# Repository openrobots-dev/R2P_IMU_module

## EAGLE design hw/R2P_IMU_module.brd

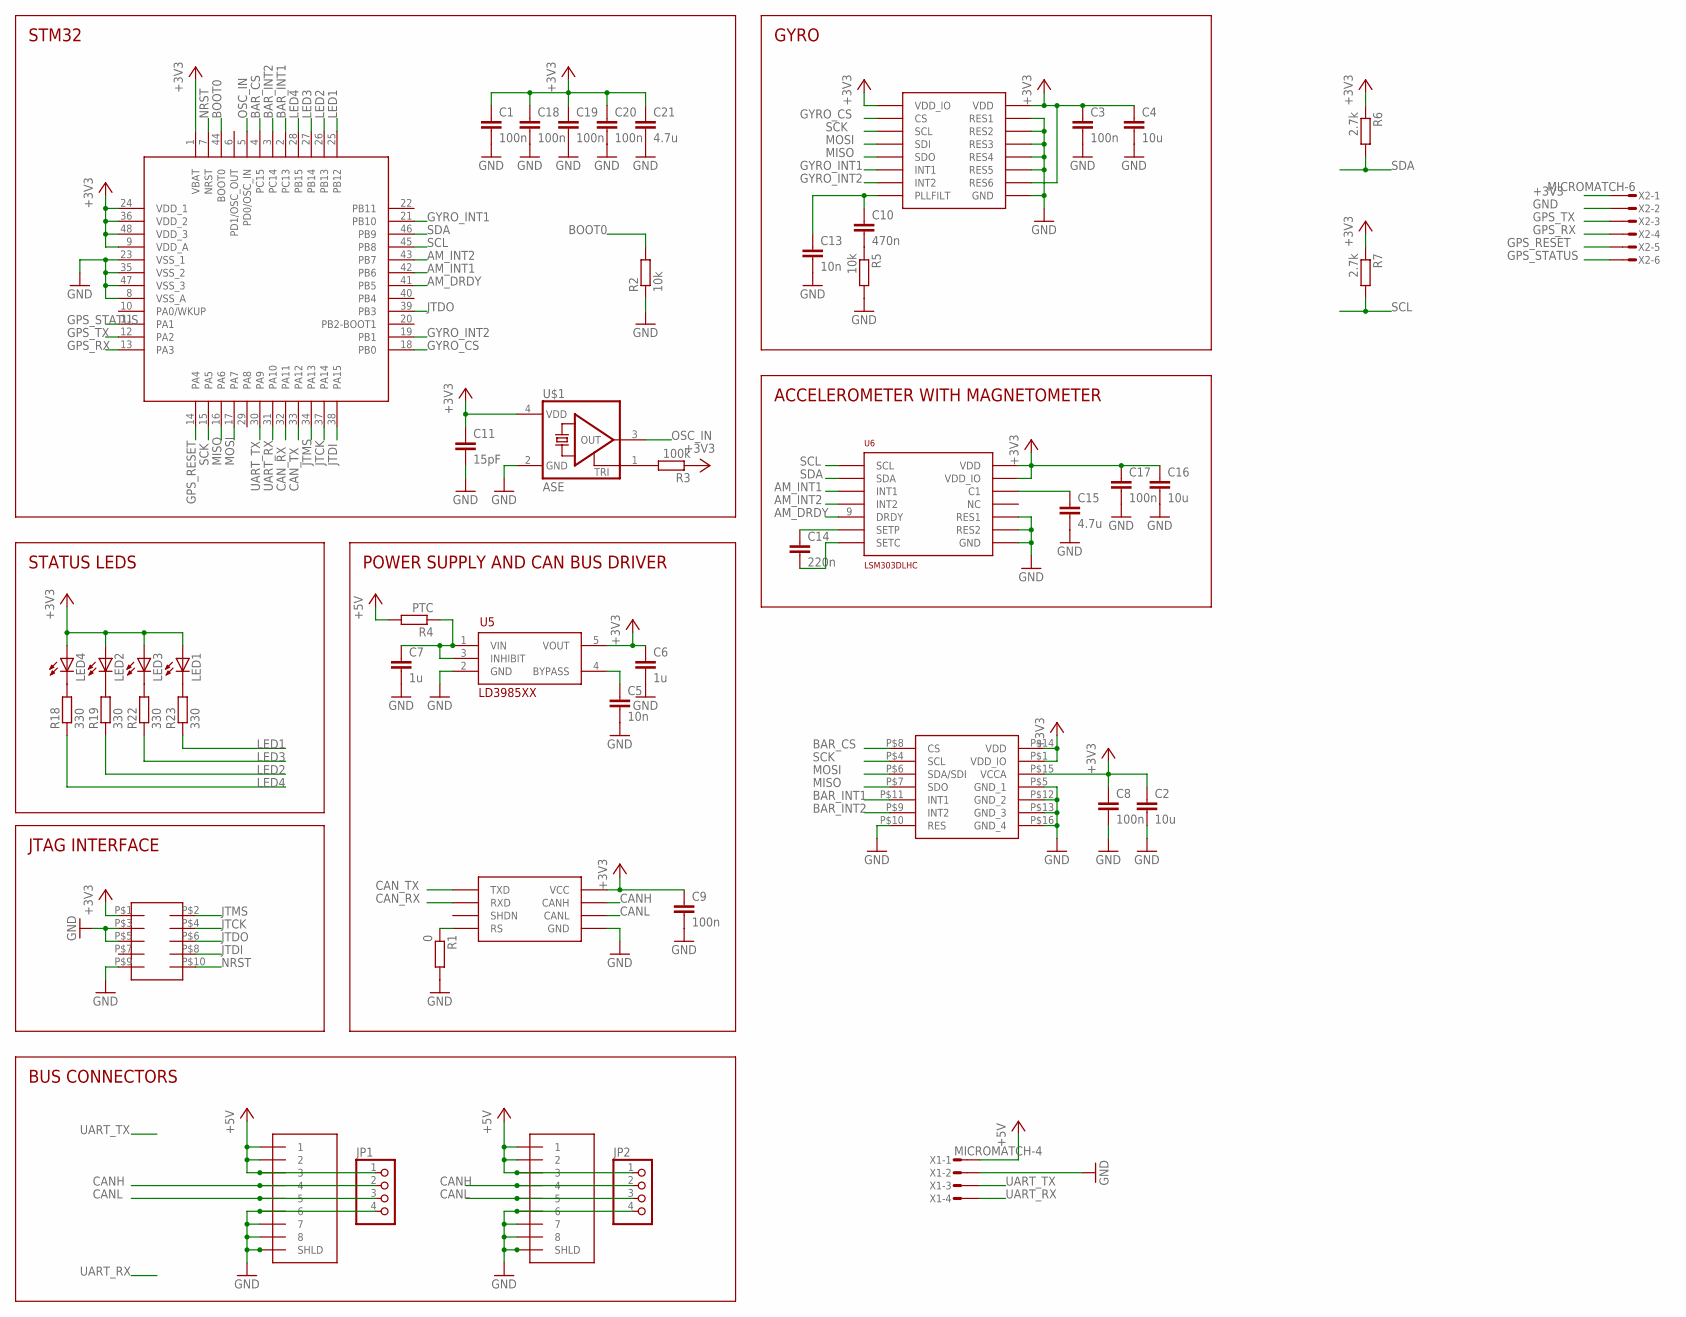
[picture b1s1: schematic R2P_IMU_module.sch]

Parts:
1, 2: RJ45-43860; 0438600010
C1, C3, C8, C9, C17, C18, C19, C20: 100n; C0603
C2, C4, C16: 10u; C0805
C5, C13: 10n; C0603
C6, C7: 1u; C0603
C10: 470n; C0603
C11: 15pF; C0603
C14: 220n; C0603
C15, C21: 4.7u; C0805
JP1, JP2: PINHD-1X4; 1X04
LED1, LED2, LED3, LED4: LEDCHIPLED_0805; CHIPLED_0805
R1: 0; R0603
R2, R5: 10k; R0603
R3: 100k; R0603
R4: PTC; R0603
R6, R7: 2.7k; R0603
R18, R19, R22, R23: 330; R0603
SOT1: MAX3051; SOT23-8L
U1: STM32F103CX; LQFP48
U2: L3G4200D; LGA16
U5: LD3985XX; SOT23-5L
U6: LSM303DLHC; LGA14
U$1: ASE
U$2: LPS331AP; HCLGA16
U$4: FTSH-105
X1: MICROMATCH-4
X2: MICROMATCH-6

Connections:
+3V3: C1.1, C2.1, C3.1, C4.1, C6.1, C8.1, C9.1, C11.1, C16.1, C17.1, C18.1, C19.1, C20.1, C21.1, LED1.A, LED2.A, LED3.A, LED4.A, R3.1, R6.1, R7.1, SOT1.P$3 (VCC), U1.1 (VBAT), U1.9 (VDD_A), U1.24 (VDD_1), U1.36 (VDD_2), U1.48 (VDD_3), U2.P$1 (VDD_IO), U2.P$15 (RES6), U2.P$16 (VDD), U5.5 (VOUT), U6.1 (VDD_IO), U6.14 (VDD), U$1.4 (VDD), U$2.P$1 (VDD_IO), U$2.P$14 (VDD), U$2.P$15 (VCCA), U$4.P$1, X2.1
+5V: 1.P$1 (1), 1.P$2 (2), 1.P$3 (3), 2.P$1 (1), 2.P$2 (2), 2.P$3 (3), JP1.1, JP2.1, R4.2, X1.1
AM_DRDY: U1.41 (PB5), U6.9 (DRDY)
AM_INT1: U1.42 (PB6), U6.5 (INT1)
AM_INT2: U1.43 (PB7), U6.4 (INT2)
BAR_CS: U1.4 (PC15), U$2.P$8 (CS)
BAR_INT1: U1.2 (PC13), U$2.P$11 (INT1)
BAR_INT2: U1.3 (PC14), U$2.P$9 (INT2)
BOOT0: R2.2, U1.44 (BOOT0)
CANH: 1.P$4 (4), 2.P$4 (4), JP1.2, JP2.2, SOT1.P$7 (CANH)
CANL: 1.P$5 (5), 2.P$5 (5), JP1.3, JP2.3, SOT1.P$6 (CANL)
CAN_RX: SOT1.P$4 (RXD), U1.32 (PA11)
CAN_TX: SOT1.P$1 (TXD), U1.33 (PA12)
GND: 1.P$6 (6), 1.P$7 (7), 1.P$8 (8), 1.P$9 (SHLD), 1.P$10, 2.P$6 (6), 2.P$7 (7), 2.P$8 (8), 2.P$9 (SHLD), 2.P$10, C1.2, C2.2, C3.2, C4.2, C5.2, C6.2, C7.2, C8.2, C9.2, C11.2, C13.2, C15.2, C16.2, C17.2, C18.2, C19.2, C20.2, C21.2, JP1.4, JP2.4, R1.2, R2.1, R5.2, SOT1.P$2 (GND), U1.8 (VSS_A), U1.23 (VSS_1), U1.35 (VSS_2), U1.47 (VSS_3), U2.P$8 (RES1), U2.P$9 (RES2), U2.P$10 (RES3), U2.P$11 (RES4), U2.P$12 (RES5), U2.P$13 (GND), U5.2 (GND), U6.7 (GND), U6.10 (RES1), U6.11 (RES2), U$1.2 (GND), U$2.P$5 (GND_1), U$2.P$10 (RES), U$2.P$12 (GND_2), U$2.P$13 (GND_3), U$2.P$16 (GND_4), U$4.P$3, U$4.P$5, U$4.P$9, X1.2, X2.2
GPS_RESET: U1.14 (PA4), X2.5
GPS_RX: U1.13 (PA3), X2.4
GPS_STATUS: U1.11 (PA1), X2.6
GPS_TX: U1.12 (PA2), X2.3
GYRO_CS: U1.18 (PB0), U2.P$5 (CS)
GYRO_INT1: U1.21 (PB10), U2.P$7 (INT1)
GYRO_INT2: U1.19 (PB1), U2.P$6 (INT2)
JTCK: U1.37 (PA14), U$4.P$4
JTDI: U1.38 (PA15), U$4.P$8
JTDO: U1.39 (PB3), U$4.P$6
JTMS: U1.34 (PA13), U$4.P$2
LED1: R23.1, U1.25 (PB12)
LED2: R19.1, U1.26 (PB13)
LED3: R22.1, U1.27 (PB14)
LED4: R18.1, U1.28 (PB15)
MISO: U1.16 (PA6), U2.P$4 (SDO), U$2.P$7 (SDO)
MOSI: U1.17 (PA7), U2.P$3 (SDI), U$2.P$6 (SDA/SDI)
unnamed: R1.1, SOT1.P$8 (RS)
unnamed: R3.2, U$1.1 (TRI)
unnamed: C5.1, U5.4 (BYPASS)
unnamed: C7.1, R4.1, U5.1 (VIN), U5.3 (INHIBIT)
unnamed: C10.2, R5.1
unnamed: C10.1, C13.1, U2.P$14 (PLLFILT)
unnamed: C14.1, U6.12 (SETP)
unnamed: LED4.C, R18.2
unnamed: C14.2, U6.13 (SETC)
unnamed: C15.1, U6.6 (C1)
unnamed: LED2.C, R19.2
unnamed: LED3.C, R22.2
unnamed: LED1.C, R23.2
NRST: U1.7 (NRST), U$4.P$10
OSC_IN: U1.5 (PD0/OSC_IN), U$1.3 (OUT)
SCK: U1.15 (PA5), U2.P$2 (SCL), U$2.P$4 (SCL)
SCL: R7.2, U1.45 (PB8), U6.2 (SCL)
SDA: R6.2, U1.46 (PB9), U6.3 (SDA)
UART_RX: U1.31 (PA10), X1.4
UART_TX: U1.30 (PA9), X1.3

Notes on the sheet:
STM32
POWER SUPPLY AND CAN BUS DRIVER
STATUS LEDS
JTAG INTERFACE
BUS CONNECTORS
ACCELEROMETER WITH MAGNETOMETER
GYRO

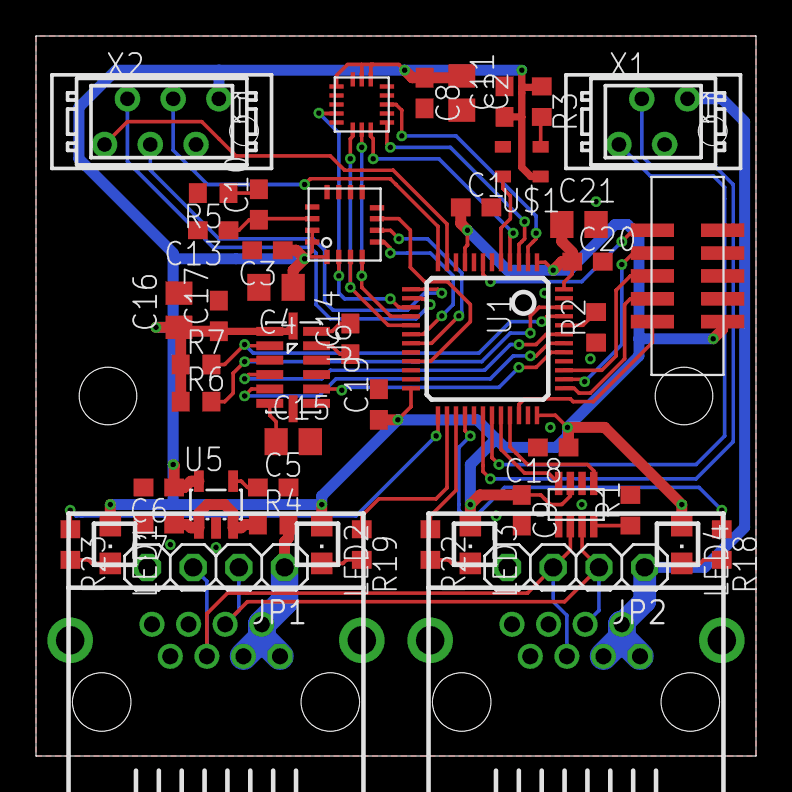
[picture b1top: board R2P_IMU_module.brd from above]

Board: 2 copper layers, 40.0 x 40.0 mm, 49 parts (0 on the bottom side), 51 nets.

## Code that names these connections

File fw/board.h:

/*
 ChibiOS/RT - Copyright (C) 2006,2007,2008,2009,2010,
 2011 Giovanni Di Sirio.

 This file is part of ChibiOS/RT.

 ChibiOS/RT is free software; you can redistribute it and/or modify
 it under the terms of the GNU General Public License as published by
 the Free Software Foundation; either version 3 of the License, or
 (at your option) any later version.

 ChibiOS/RT is distributed in the hope that it will be useful,
 but WITHOUT ANY WARRANTY; without even the implied warranty of
 MERCHANTABILITY or FITNESS FOR A PARTICULAR PURPOSE.  See the
 GNU General Public License for more details.

 You should have received a copy of the GNU General Public License
 along with this program.  If not, see <http://www.gnu.org/licenses/>.
 */

#ifndef _BOARD_H_
#define _BOARD_H_

/*
 * Setup for the R2D IMU module.
 */

/*
 * Board identifier.
 */
#define BOARD_R2P_IMU_MODULE
#define BOARD_NAME              "R2P IMU module"

/*
 * Board frequencies.
 */
#define STM32_LSECLK            32768
#define STM32_HSECLK            8000000

/*
 * MCU type, supported types are defined in ./os/hal/platforms/hal_lld.h.
 */
#define STM32F10X_MD
#define STM32F10X

/*
 * IO pins assignments.
 */
#define LED1_GPIO				GPIOB
#define LED1					12
#define LED2_GPIO				GPIOB
#define LED2					13
#define LED3_GPIO				GPIOB
#define LED3					14
#define LED4_GPIO				GPIOB
#define LED4					15

#define SERIAL_DRIVER           SD1
//#define GPS_SERIAL_DRIVER       SD2
#define SPI_DRIVER              SPID1
#define I2C_DRIVER              I2CD1

#define GYRO_GPIO               GPIOB
#define GYRO_CS                 0
#define GYRO_INT1               10
#define GYRO_INT2               1

#define AM_GPIO                 GPIOB
#define AM_DRDY                 5
#define AM_INT1                 6
#define AM_INT2                 7

#define GPS_GPIO                GPIOA
#define GPS_STATUS              1

#define TEST_GPIO               GPIOA
#define TEST1                   1
#define TEST2                   4


/*
 * I/O ports initial setup, this configuration is established soon after reset
 * in the initialization code.
 *
 * The digits have the following meaning:
 *   0 - Analog input.
 *   1 - Push Pull output 10MHz.
 *   2 - Push Pull output 2MHz.
 *   3 - Push Pull output 50MHz.
 *   4 - Digital input.
 *   5 - Open Drain output 10MHz.
 *   6 - Open Drain output 2MHz.
 *   7 - Open Drain output 50MHz.
 *   8 - Digital input with PullUp or PullDown resistor depending on ODR.
 *   9 - Alternate Push Pull output 10MHz.
 *   A - Alternate Push Pull output 2MHz.
 *   B - Alternate Push Pull output 50MHz.
 *   C - Reserved.
 *   D - Alternate Open Drain output 10MHz.
 *   E - Alternate Open Drain output 2MHz.
 *   F - Alternate Open Drain output 50MHz.
 * Please refer to the STM32 Reference Manual for details.
 */

/*
 * Port A setup.
 * Everything input with pull-up except:
 * PA1  - Digital input (GPS_STATUS).
 * PA2  - Alternate output (USART2 TX).
 * PA3  - Normal input     (USART2 RX).
 * PA4  - Push Pull output (GPS_RESET).
 * PA5  - Alternate output (SPI1 SCK).
 * PA6  - Normal input     (SPI1 MISO).
 * PA7  - Alternate output (SPI1 MOSI).
 * PA9  - Alternate output (USART1 TX).
 * PA10 - Normal input     (USART1 RX).
 * PA11 - Normal input     (CAN1 RX).
 * PA12 - Alternate output (CAN1 TX).
 */
#define VAL_GPIOACRL            0xB4B34B38      /*  PA7...PA0 */ /* XXX GPS_STATUS ORA E' COME OUTPUT DI TEST! */
#define VAL_GPIOACRH            0x888B44B8      /* PA15...PA8 */
#define VAL_GPIOAODR            0xFFFFFFFF

/*
 * Port B setup.
 * Everything input with pull-up except:
 *
 * PB0 - Push Pull output (GYRO_CS).
 * PB1  - Normal input (GYRO_INT2).
 * PB5  - Normal input (AM_DRDY).
 * PB6  - Normal input (AM_INT1).
 * PB7  - Normal input (AM_INT2).
 * PB8  - Alternate Open Drain output (I2C1 SCL remapped).
 * PB9  - Alternate Open Drain output (I2C1 SDA remapped).
 * PB10 - Normal input (GYRO_INT1).
 * PB12 - Push Pull output (LED1).
 * PB13 - Push Pull output (LED2).
 * PB14 - Push Pull output (LED3).
 * PB15 - Push Pull output (LED4).
 */
#define VAL_GPIOBCRL            0x88844443      /*  PB7...PB0 */
#define VAL_GPIOBCRH            0x333384FF      /* PB15...PB8 */
#define VAL_GPIOBODR            0xFFFFFFFF

/*
 * Port C setup.
 * Everything input with pull-up except:
 */
#define VAL_GPIOCCRL            0x88888888      /*  PC7...PC0 */
#define VAL_GPIOCCRH            0x88888888      /* PC15...PC8 */
#define VAL_GPIOCODR            0xFFFFFFFF

#if !defined(_FROM_ASM_)
#ifdef __cplusplus
extern "C" {
#endif
void boardInit(void);
#ifdef __cplusplus
}
#endif
#endif /* _FROM_ASM_ */

#endif /* _BOARD_H_ */

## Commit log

2012-07-30 Datasheets
2012-07-30 File rename
2012-07-30 Initial schematics commit
2012-07-30 .gitignore added to revision control
2012-07-30 Ongoing layout
2012-07-31 Board layout finished
2012-09-21 Firmware initial commit
2012-09-21 Added eclipse .project file
2012-09-21 Bugfix
2012-09-22 Firmware ported to ChibiOS/RT 2.5.0
    Andrea Zoppi
2012-10-08 Moved test firmware under test/
2012-10-08 Eclipse default and test make targets working
2012-10-08 IMU with RTCAN initial commit
2012-10-08 Moved .project outside test directory
2012-10-25 sraw() update to print _really raw_ data
2012-10-26 Fixed accelerometer data alignment
2013-06-21 Cleanup and middleware demo
2013-06-21 Updated demo main files
2013-06-21 Added license files
2013-09-24 new branch
2013-09-24 setting up tiltone mw_v2
2013-09-25 ported to mw v2
2013-09-26 remote bootloader test firmware
2013-09-26 added name to debug transport
2013-09-29 shared nodes
2013-10-02 merged filtering
2013-10-03 added LEDx_GPIO definitions
2013-10-04 balance control working
2013-10-04 added LEDx_GPIO defines
2013-10-10 added templated PID
2013-10-12 velocity control working
2013-10-16 fixed demo
2013-10-24 schematics reorganized
2013-10-24 added .dep/
2013-10-25 Project update
2013-10-25 Added .gitignore
2013-10-25 added madgwick_imu
2013-10-30 moved to newest mw
2013-11-25 soft control parameters
2013-11-29 added utils
2014-01-09 removed balance stuff
2014-02-20 tuned PID
2014-02-20 performed calibration
2014-05-20 Added comment with configured ODR
2014-10-20 added odometry
2015-03-09 Updated controller to new basketbot revision
